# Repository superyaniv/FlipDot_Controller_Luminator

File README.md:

# FlipDot Controller Project

A FlipDot board was a unique way, before the cheap and ubiquitous LED displays, to display signage with low power and high visability. The unique innovation combines electrical engineering princples of electromagnetism, polarity, multiplexing, and much more. Not to mention it's just fun to see the complex mechanical switching in realtime. As I became interested in learning more about electrical engineering and design, this project, created in 2011 and posted on my public git recently, inspired me to begin learning circuit design. 

## Getting Started

The PCB schemetic uses 10 shift registers to drive darlington array source and pull down ICs. The pin layout is explained in the cvs file. From there, the project uses the flipdot controller python class to post bytes to the board and pin layout. The layer of abstraction above that can be a variance of code, depending on what to pull and post to the board. Examples included here are a clock, bitcoin price feed, and twitter display.

### Prerequisites

Hardware necessary to complete the code from scratch include:

```
10 x 595 Shift Registers
5 x ULN2803 Darlington Arrays
5 x Source Drivers (x2981)
Note: A different layout could use MOSFET transistors instead of these ICs.

1 x microcontroller (RPI or ESP8266 for use with this python code or Arduino )
```

### View of the PCB

Top, Bottom, and overall Design View of the PCB:

### Installing

Using the gerber files, you can have the board made at a host of pcb manufacturers. Alternatively you can design the board yourself with a breadboard.

Set up the layout of the board:

```
Using the gerber files, you can have the board made at a host of pcb manufacturers. 

Alternatively you can design the board yourself with a breadboard.
```

Wire your board:

```
Wire the board according to the schematic.

Connect the board to the flip-dot display and the microcontroller.
(use pins 18, 23, and 24 for the shift register data, clock, clear)
```

Connect to Power:

```
Connect the board to power, 9V for to drive the dots, and 5V to the registers.
```

End with an example of getting some data out of the system or using it for a little demo

## Running the tests

Run tests to the shift registers first, to ensure the correct outputs from the registers.

Run tests to the source and pull drivers, to ensure the 9V supply is being triggered to the dots.

Use the attached LEDs to check power to the board.

If you are using APIs to get input for the display, check the output of those APIs by uncommenting the debug and print lines.

## Deployment

Add additional notes about how to deploy this on a live system

## Authors

Yaniv Joseph Alfasy (https://yanivalfasy.com)

Please contact me if you have any additional questions.

## License

No licensing decided yet.

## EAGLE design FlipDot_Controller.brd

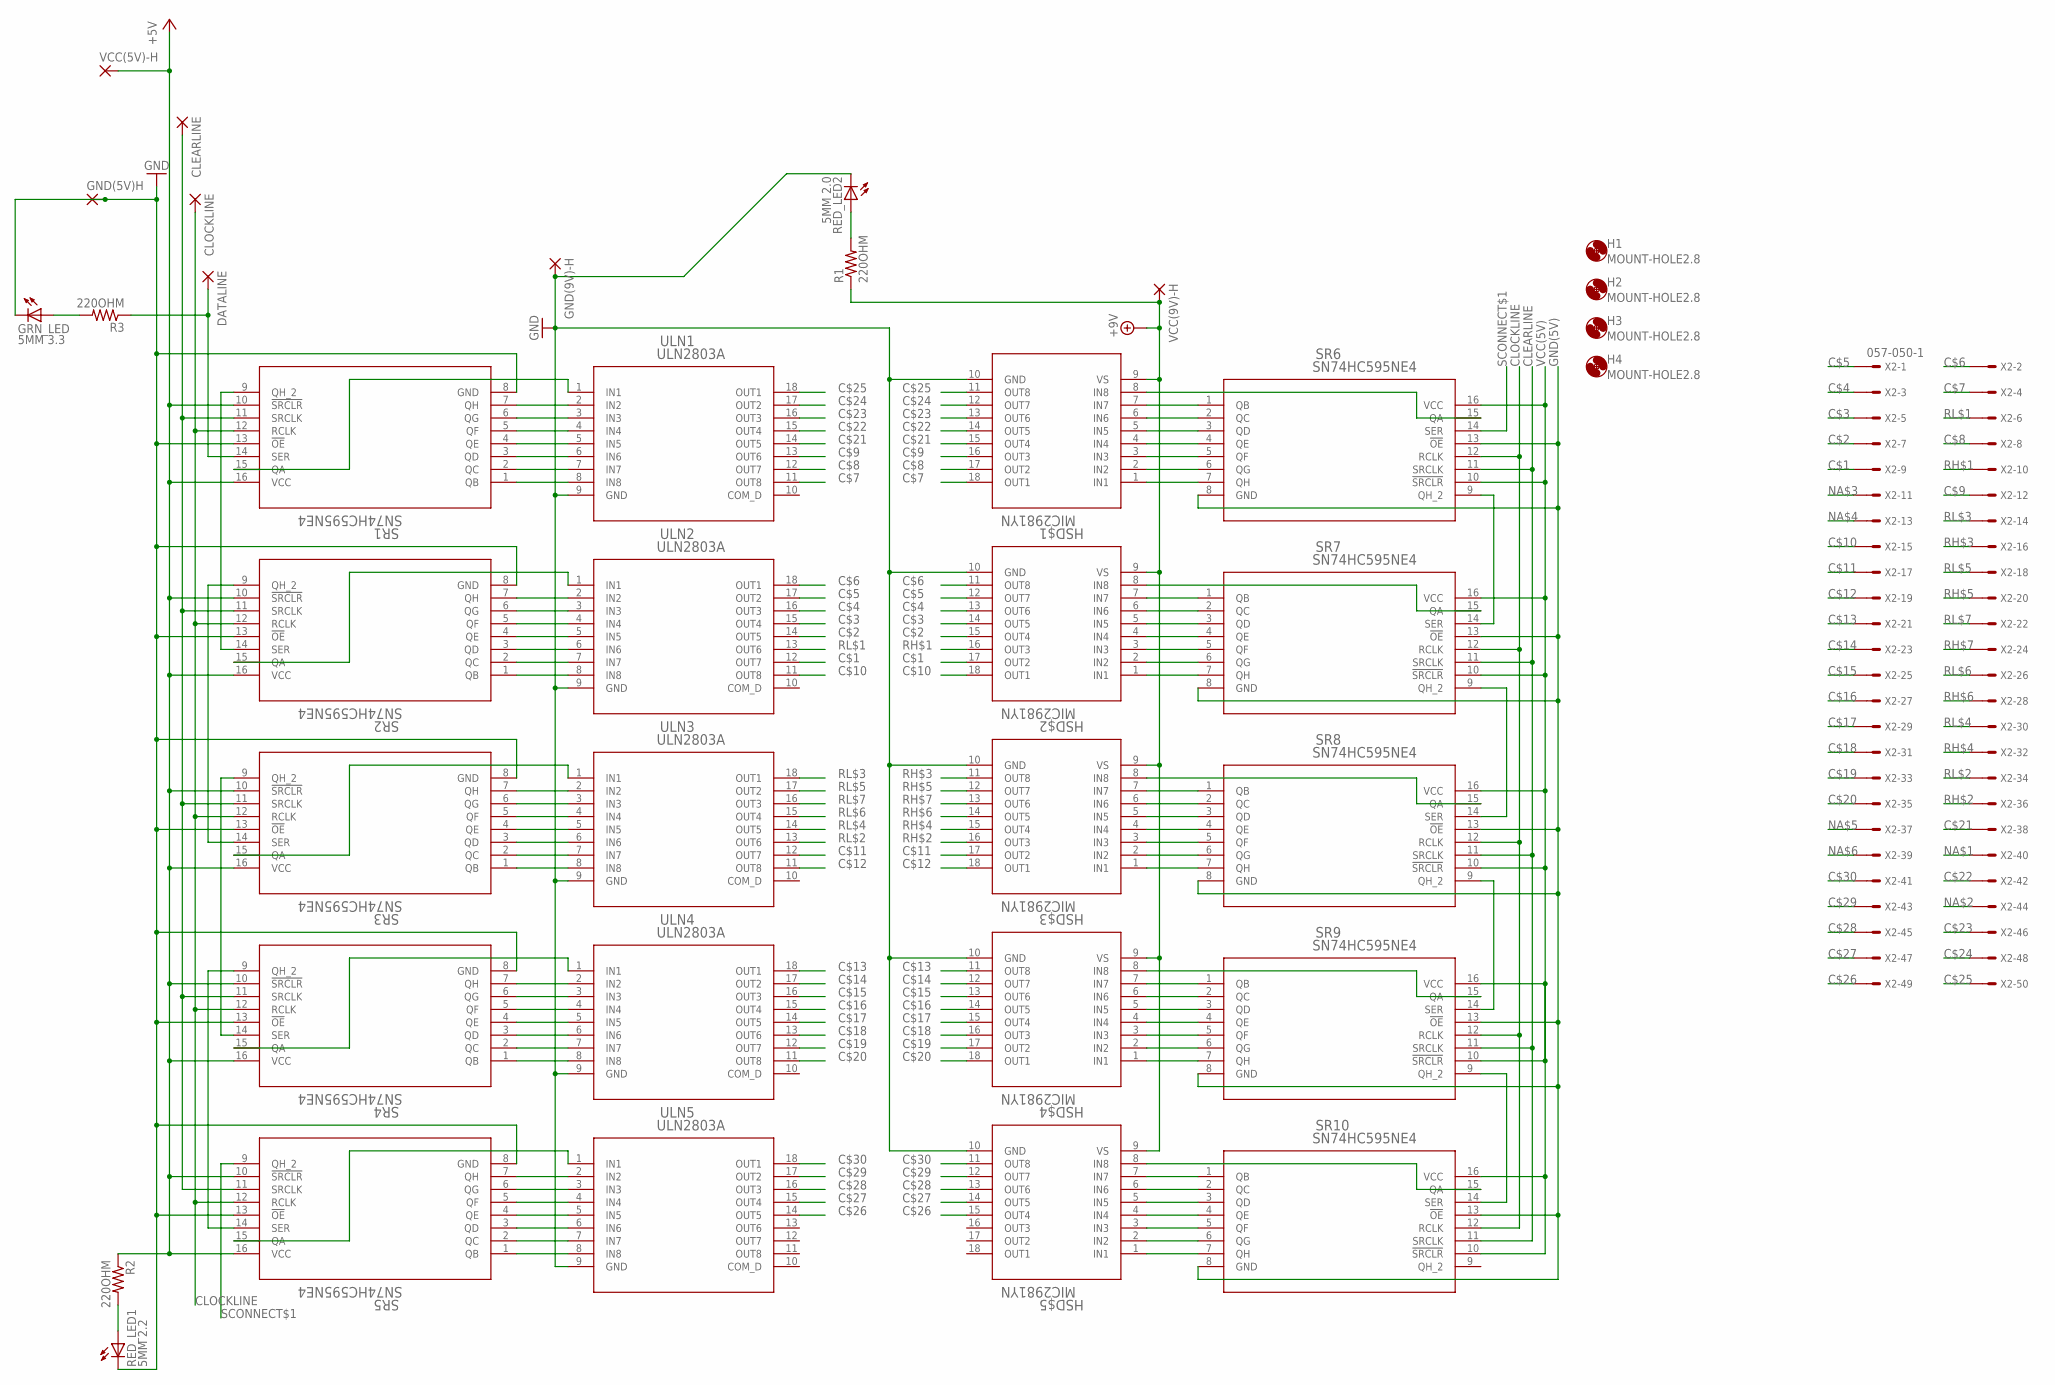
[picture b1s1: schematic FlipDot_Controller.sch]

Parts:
CLEARLINE: WIREPAD1,6/0,8; 1,6/0,8
CLOCKLINE: WIREPAD1,6/0,8; 1,6/0,8
DATALINE: WIREPAD1,6/0,8; 1,6/0,8
GND(5V)H, GND(9V)-H: WIREPAD1,6/0,8; 1,6/0,8
GRN_LED: 5MM 3.3; LED5MM
H1, H2, H3, H4: MOUNT-HOLE2.8; 2,8
HSD$1, HSD$2, HSD$3, HSD$4, HSD$5: MIC2981YN; PDIP-18
R1, R2, R3: 220OHM; 0204/7
RED_LED1: 5MM 2.2; LED5MM
RED_LED2: 5MM 2.0; LED5MM
SR1, SR2, SR3, SR4, SR5, SR6, SR7, SR8, SR9, SR10: SN74HC595NE4; N16
ULN1, ULN2, ULN3, ULN4, ULN5: ULN2803A; DIP-18
VCC(5V)-H, VCC(9V)-H: WIREPAD1,6/0,8; 1,6/0,8
X2: 057-050-1

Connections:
+9V: HSD$1.9 (VS), HSD$2.9 (VS), HSD$3.9 (VS), HSD$4.9 (VS), HSD$5.9 (VS), R1.1, VCC(9V)-H.1
C$1: HSD$2.17 (OUT2), ULN2.12 (OUT7), X2.9
C$2: HSD$2.15 (OUT4), ULN2.14 (OUT5), X2.7
C$3: HSD$2.14 (OUT5), ULN2.15 (OUT4), X2.5
C$4: HSD$2.13 (OUT6), ULN2.16 (OUT3), X2.3
C$5: HSD$2.12 (OUT7), ULN2.17 (OUT2), X2.1
C$6: HSD$2.11 (OUT8), ULN2.18 (OUT1), X2.2
C$7: HSD$1.18 (OUT1), ULN1.11 (OUT8), X2.4
C$8: HSD$1.17 (OUT2), ULN1.12 (OUT7), X2.8
C$9: HSD$1.16 (OUT3), ULN1.13 (OUT6), X2.12
C$10: HSD$2.18 (OUT1), ULN2.11 (OUT8), X2.15
C$11: HSD$3.17 (OUT2), ULN3.12 (OUT7), X2.17
C$12: HSD$3.18 (OUT1), ULN3.11 (OUT8), X2.19
C$13: HSD$4.11 (OUT8), ULN4.18 (OUT1), X2.21
C$14: HSD$4.12 (OUT7), ULN4.17 (OUT2), X2.23
C$15: HSD$4.13 (OUT6), ULN4.16 (OUT3), X2.25
C$16: HSD$4.14 (OUT5), ULN4.15 (OUT4), X2.27
C$17: HSD$4.15 (OUT4), ULN4.14 (OUT5), X2.29
C$18: HSD$4.16 (OUT3), ULN4.13 (OUT6), X2.31
C$19: HSD$4.17 (OUT2), ULN4.12 (OUT7), X2.33
C$20: HSD$4.18 (OUT1), ULN4.11 (OUT8), X2.35
C$21: HSD$1.15 (OUT4), ULN1.14 (OUT5), X2.38
C$22: HSD$1.14 (OUT5), ULN1.15 (OUT4), X2.42
C$23: HSD$1.13 (OUT6), ULN1.16 (OUT3), X2.46
C$24: HSD$1.12 (OUT7), ULN1.17 (OUT2), X2.48
C$25: HSD$1.11 (OUT8), ULN1.18 (OUT1), X2.50
C$26: HSD$5.15 (OUT4), ULN5.14 (OUT5), X2.49
C$27: HSD$5.14 (OUT5), ULN5.15 (OUT4), X2.47
C$28: HSD$5.13 (OUT6), ULN5.16 (OUT3), X2.45
C$29: HSD$5.12 (OUT7), ULN5.17 (OUT2), X2.43
C$30: HSD$5.11 (OUT8), ULN5.18 (OUT1), X2.41
CLEARLINE: CLEARLINE.1, SR1.11 (SRCLK), SR2.11 (SRCLK), SR3.11 (SRCLK), SR4.11 (SRCLK), SR5.11 (SRCLK), SR6.11 (SRCLK), SR7.11 (SRCLK), SR8.11 (SRCLK), SR9.11 (SRCLK), SR10.11 (SRCLK)
CLOCKLINE: CLOCKLINE.1, SR1.12 (RCLK), SR2.12 (RCLK), SR3.12 (RCLK), SR4.12 (RCLK), SR5.12 (RCLK), SR6.12 (RCLK), SR7.12 (RCLK), SR8.12 (RCLK), SR9.12 (RCLK), SR10.12 (RCLK)
DATALINE: DATALINE.1, R3.1, SR1.14 (SER)
GND(5V): GND(5V)H.1, GRN_LED.K (C), RED_LED1.K (C), SR1.8 (GND), SR1.13 (!OE), SR2.8 (GND), SR2.13 (!OE), SR3.8 (GND), SR3.13 (!OE), SR4.8 (GND), SR4.13 (!OE), SR5.8 (GND), SR5.13 (!OE), SR6.8 (GND), SR6.13 (!OE), SR7.8 (GND), SR7.13 (!OE), SR8.8 (GND), SR8.13 (!OE), SR9.8 (GND), SR9.13 (!OE), SR10.8 (GND), SR10.13 (!OE)
GND(9V): GND(9V)-H.1, HSD$1.10 (GND), HSD$2.10 (GND), HSD$3.10 (GND), HSD$4.10 (GND), HSD$5.10 (GND), RED_LED2.K (C), ULN1.9 (GND), ULN2.9 (GND), ULN3.9 (GND), ULN4.9 (GND), ULN5.9 (GND)
unnamed: SR1.15 (QA), ULN1.1 (IN1)
unnamed: SR1.1 (QB), ULN1.8 (IN8)
unnamed: SR1.2 (QC), ULN1.7 (IN7)
unnamed: SR1.3 (QD), ULN1.6 (IN6)
unnamed: SR1.4 (QE), ULN1.5 (IN5)
unnamed: SR1.5 (QF), ULN1.4 (IN4)
unnamed: SR1.6 (QG), ULN1.3 (IN3)
unnamed: SR1.9 (QH_2), SR2.14 (SER)
unnamed: SR1.7 (QH), ULN1.2 (IN2)
unnamed: SR6.9 (QH_2), SR7.14 (SER)
unnamed: SR7.9 (QH_2), SR8.14 (SER)
unnamed: SR8.9 (QH_2), SR9.14 (SER)
unnamed: SR2.15 (QA), ULN2.1 (IN1)
unnamed: SR2.9 (QH_2), SR3.14 (SER)
unnamed: SR4.15 (QA), ULN4.1 (IN1)
unnamed: SR2.7 (QH), ULN2.2 (IN2)
unnamed: SR2.6 (QG), ULN2.3 (IN3)
unnamed: SR2.5 (QF), ULN2.4 (IN4)
unnamed: SR2.4 (QE), ULN2.5 (IN5)
unnamed: SR2.3 (QD), ULN2.6 (IN6)
unnamed: SR2.2 (QC), ULN2.7 (IN7)
unnamed: SR3.15 (QA), ULN3.1 (IN1)
unnamed: SR3.9 (QH_2), SR4.14 (SER)
unnamed: SR4.9 (QH_2), SR5.14 (SER)
unnamed: SR5.15 (QA), ULN5.1 (IN1)
unnamed: SR4.7 (QH), ULN4.2 (IN2)
unnamed: SR3.7 (QH), ULN3.2 (IN2)
unnamed: SR3.6 (QG), ULN3.3 (IN3)
unnamed: SR3.5 (QF), ULN3.4 (IN4)
unnamed: SR3.4 (QE), ULN3.5 (IN5)
unnamed: SR3.3 (QD), ULN3.6 (IN6)
unnamed: SR3.2 (QC), ULN3.7 (IN7)
unnamed: HSD$1.8 (IN8), SR6.15 (QA)
unnamed: SR5.7 (QH), ULN5.2 (IN2)
unnamed: HSD$1.7 (IN7), SR6.1 (QB)
unnamed: HSD$1.6 (IN6), SR6.2 (QC)
unnamed: SR4.6 (QG), ULN4.3 (IN3)
unnamed: SR4.5 (QF), ULN4.4 (IN4)
unnamed: SR4.4 (QE), ULN4.5 (IN5)
unnamed: SR4.3 (QD), ULN4.6 (IN6)
unnamed: SR4.2 (QC), ULN4.7 (IN7)
unnamed: SR4.1 (QB), ULN4.8 (IN8)
unnamed: SR5.6 (QG), ULN5.3 (IN3)
unnamed: HSD$1.5 (IN5), SR6.3 (QD)
unnamed: HSD$1.4 (IN4), SR6.4 (QE)
unnamed: SR5.5 (QF), ULN5.4 (IN4)
unnamed: SR5.4 (QE), ULN5.5 (IN5)
unnamed: SR5.3 (QD), ULN5.6 (IN6)
unnamed: SR5.2 (QC), ULN5.7 (IN7)
unnamed: SR5.1 (QB), ULN5.8 (IN8)
unnamed: HSD$1.3 (IN3), SR6.5 (QF)
unnamed: HSD$1.2 (IN2), SR6.6 (QG)
unnamed: HSD$1.1 (IN1), SR6.7 (QH)
unnamed: SR9.9 (QH_2), SR10.14 (SER)
unnamed: HSD$2.8 (IN8), SR7.15 (QA)
unnamed: HSD$3.8 (IN8), SR8.15 (QA)
unnamed: HSD$4.8 (IN8), SR9.15 (QA)
unnamed: HSD$5.8 (IN8), SR10.15 (QA)
unnamed: HSD$2.7 (IN7), SR7.1 (QB)
unnamed: HSD$2.6 (IN6), SR7.2 (QC)
unnamed: HSD$2.5 (IN5), SR7.3 (QD)
unnamed: HSD$2.4 (IN4), SR7.4 (QE)
unnamed: HSD$2.3 (IN3), SR7.5 (QF)
unnamed: HSD$2.2 (IN2), SR7.6 (QG)
unnamed: HSD$2.1 (IN1), SR7.7 (QH)
unnamed: HSD$3.7 (IN7), SR8.1 (QB)
unnamed: HSD$3.6 (IN6), SR8.2 (QC)
unnamed: HSD$3.5 (IN5), SR8.3 (QD)
unnamed: HSD$3.4 (IN4), SR8.4 (QE)
unnamed: HSD$3.3 (IN3), SR8.5 (QF)
unnamed: HSD$3.2 (IN2), SR8.6 (QG)
unnamed: HSD$3.1 (IN1), SR8.7 (QH)
unnamed: HSD$4.7 (IN7), SR9.1 (QB)
unnamed: HSD$4.6 (IN6), SR9.2 (QC)
unnamed: HSD$4.5 (IN5), SR9.3 (QD)
unnamed: HSD$4.4 (IN4), SR9.4 (QE)
unnamed: HSD$4.3 (IN3), SR9.5 (QF)
unnamed: HSD$4.2 (IN2), SR9.6 (QG)
unnamed: HSD$4.1 (IN1), SR9.7 (QH)
unnamed: HSD$5.7 (IN7), SR10.1 (QB)
unnamed: HSD$5.6 (IN6), SR10.2 (QC)
unnamed: HSD$5.5 (IN5), SR10.3 (QD)
unnamed: HSD$5.4 (IN4), SR10.4 (QE)
unnamed: HSD$5.3 (IN3), SR10.5 (QF)
unnamed: HSD$5.2 (IN2), SR10.6 (QG)
unnamed: HSD$5.1 (IN1), SR10.7 (QH)
unnamed: SR2.1 (QB), ULN2.8 (IN8)
unnamed: SR3.1 (QB), ULN3.8 (IN8)
unnamed: R2.2, RED_LED1.A
unnamed: R1.2, RED_LED2.A
unnamed: GRN_LED.A, R3.2
NA$1: X2.40
NA$2: X2.44
NA$3: X2.11
NA$4: X2.13
NA$5: X2.37
NA$6: X2.39
RH$1: HSD$2.16 (OUT3), X2.10
RH$2: HSD$3.16 (OUT3), X2.36
RH$3: HSD$3.11 (OUT8), X2.16
RH$4: HSD$3.15 (OUT4), X2.32
RH$5: HSD$3.12 (OUT7), X2.20
RH$6: HSD$3.14 (OUT5), X2.28
RH$7: HSD$3.13 (OUT6), X2.24
RL$1: ULN2.13 (OUT6), X2.6
RL$2: ULN3.13 (OUT6), X2.34
RL$3: ULN3.18 (OUT1), X2.14
RL$4: ULN3.14 (OUT5), X2.30
RL$5: ULN3.17 (OUT2), X2.18
RL$6: ULN3.15 (OUT4), X2.26
RL$7: ULN3.16 (OUT3), X2.22
SCONNECT$1: SR5.9 (QH_2), SR6.14 (SER)
VCC(5V): R2.1, SR1.10 (!SRCLR), SR1.16 (VCC), SR2.10 (!SRCLR), SR2.16 (VCC), SR3.10 (!SRCLR), SR3.16 (VCC), SR4.10 (!SRCLR), SR4.16 (VCC), SR5.10 (!SRCLR), SR5.16 (VCC), SR6.10 (!SRCLR), SR6.16 (VCC), SR7.10 (!SRCLR), SR7.16 (VCC), SR8.10 (!SRCLR), SR8.16 (VCC), SR9.10 (!SRCLR), SR9.16 (VCC), SR10.10 (!SRCLR), SR10.16 (VCC), VCC(5V)-H.1

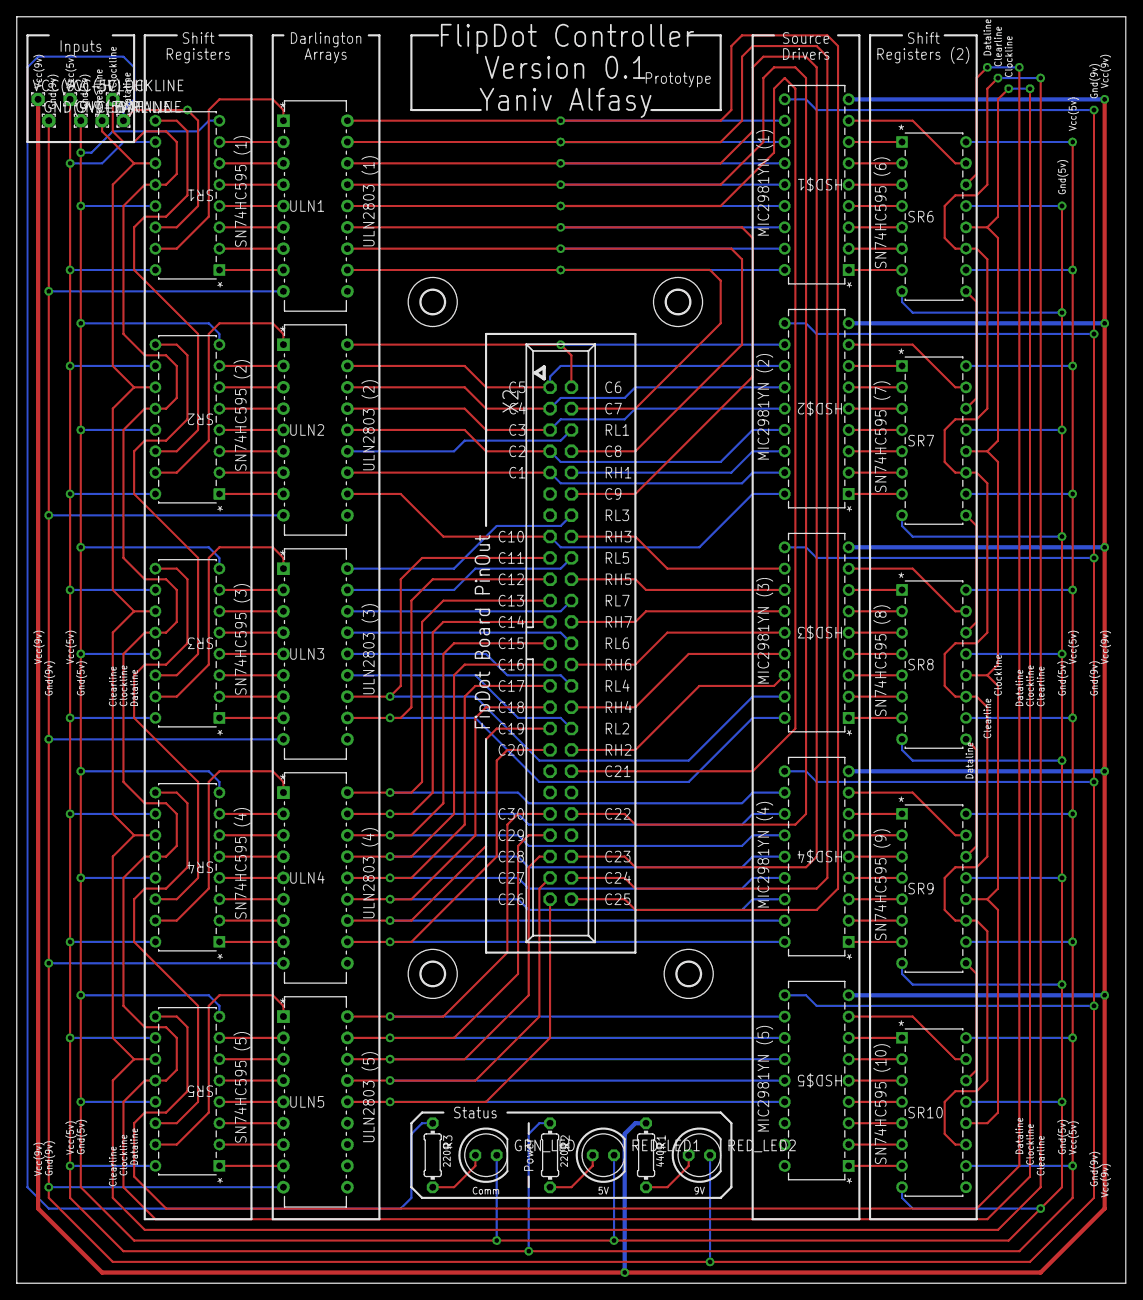
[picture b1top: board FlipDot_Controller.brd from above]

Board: 2 copper layers, 132.1 x 150.8 mm, 38 parts (0 on the bottom side), 143 nets.

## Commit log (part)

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2017-12-09 Added board and schematic - as well as pin layout file.
2017-12-09 Updated titles.
2017-12-10 Updated File Structure.
2017-12-10 Adding temporary controller file - to update with class structure.
2017-12-10 Added Gerber-generated pictures of PCB layout.
2017-12-10 Added PCB Gerber Files
2017-12-10 Updated Drill Files
2017-12-10 Updated Gerber Png Files
2017-12-10 Updated Board Design for Graphics.
2017-12-10 Added csv layout.
2017-12-10 Updated layout CSV for real Socket pin numbers.
2017-12-10 Updated python controller files, classes, and tests.
2017-12-10 Updated pictures in README.md
2017-12-27 Updated to RPi from wiringpi
2017-12-27 Updated from wiringpi to RPi.GPIO
2017-12-27 Updated methods in class
2017-12-27 Adding counter test
2017-12-27 Updating to change length of display message
2017-12-27 added state history to controller class.
2017-12-27 adding scroller test.
2017-12-27 updated flipdot tests.
2017-12-27 updating scroller test.
2017-12-27 updating for scroller.
2017-12-27 updating updateDisplay.
2017-12-27 updating scroller test to do one column.
2017-12-27 updating segment in controller class.
2017-12-27 updating controller for offset scroller.
2017-12-27 updating cleardots function.
2017-12-27 updating multipanel threading
2017-12-27 Fixing range error in update display.
2017-12-27 Fixing Thread looping.
2017-12-29 updating index range problem in controller class.
2017-12-29 Testing scroller.
2017-12-31 updating secondary pin layout
2018-01-01 Updating for multipanel
2018-01-02 Updating for multi panel
2018-01-04 Updating FlipDot for new voltage and multipanel.
2018-01-06 Updating all files for cleanpup of old pin layouts.
2018-01-07 removed old flipdottest.py
2018-01-07 Adding multi process testing
2020-09-28 updated for 5 segment small electro mag
2020-09-28 updated tests - ran them - and checked the display... getting some flipping power issues - but assume it is becasue of the connection to the pad...
2020-09-28 updated for removing delay redundancies - see vm
2020-09-29 adding new branch to check diff
2020-10-12 updates for multipanel
